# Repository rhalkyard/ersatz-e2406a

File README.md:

# Ersatz E2406A - a logic analyzer breakout for the Macintosh 68030 PDS slot

Logic analyzer adapter board for the Macintosh 68030 PDS slot, loosely based on
the [HP
E2406A](http://bitsavers.org/test_equipment/hp/logic_analyzer_preprocessors/E2406-97004_68030_Analysis_Probe_200106.pdf)
68030 analysis probe.

## Bill of materials

| Reference | Quantity | Description                                      | Digikey P/N  |
| --------- | -------- | ------------------------------------------------ | ------------ |
| J1        | 1        | DIN 41612 120 pin male connector, right-angle    | A1277-ND     |
| J2        | 1        | DIN 41612 120 pin female connector, right-angle  | A32307-ND    |
| J3-J7     | 5        | Surface-mount IDC header, 2.54mm pitch, 2x10 pin | 1175-1623-ND |

J2 is only required if additional PDS cards are to be connected.

## Compatibility

Tested and verified to work on the Macintosh SE/30.

Works (with limitations described below) on the Macintosh IIfx.

Should in theory work on the Macintosh IIsi, but has not been tested, and will
probably not fit without removing the logic board from the case.

### Logic Analyzer requirements

This adapter should be compatible with any HP logic analyzer having at least 80
channels (i.e. 5 or more pods). I have personally been using it with a 1650B and
1652B, but a 1660- or 1670-series analyzer should work just as well (or better)
so long as it has enough channels.

While it is possible to connect this board to a logic analyzer using flying-lead
pods, it is designed to be used with HP 01650-63203 "termination adapters" that
connect using 20-pin 0.1"-pitch connectors. I have also designed [a DIY
substitute](https://github.com/rhalkyard/hp-logic-analyzer-termination-adapter)
for these adapters, since they were an optional extra and most analyzers do not
come with them.

## Differences to the original E2406A

The original E2406A analysis probe is a board that interposes between the CPU
and CPU socket. Given the height of components surrounding the CPU socket on
Macintosh logic boards, it is unlikely that it would fit as intended on a
Macintosh. Instead, this adapter plugs into the 68030 PDS slot, which exposes
_almost_ the entire 68030 processor bus. The `/CIIN` and `/REFILL` signals are
not present on the PDS connector, but the absence of these signals does not have
significant bearing on analysis - on Macintosh systems, `/CIIN` is tied high,
and the `/REFILL` signal from the processor just provides additional low-level
information on the pipeline state.

The E2406A is an active probe with buffers on its logic analyzer outputs in
order to lessen its impact on signal integrity. In the interests of simplicity
(and cost), this adapter omits those buffers. On stock or minimally-expanded
machines, this appears to be no issue, but machines with large numbers of
expansion cards may experience instability.

The E2406A also has active logic to assist the analyzer in capturing accesses
that use the 68030's burst mode. This adapter omits this logic, and is unable to
correctly capture burst-mode accesses (only the final longword will be
captured). The only Macintosh to use burst mode is the IIfx, and as described
below, the architecture of the IIfx means that memory accesses cannot be
observed from the PDS slot anyway, so the lack of burst nmode support is moot in
this application.

## Limitations in use with the Macintosh IIfx

The architecture of the Macintosh IIfx imposes significant limitations on the
operation of this adapter. While on other machines, the PDS slot is connected
directly to the CPU and can fully 'observe' all bus transactions, the PDS slot
on the IIfx is on a buffered 'slow bus' separate from main memory and shared
only with NuBus and onboard I/O devices. As a result, when used on the IIfx,
this adapter can only capture accesses to PDS, NuBus and onboard I/O devices, and
cannot capture accesses to RAM or ROM.

## Configuration

Signals on the 5 20-pin pod connectors are assigned as below - note that the pod
assignments are somewhat arbitrary, but are set up to match the assignments
documented for the E2406A preprocessor.

| Pin | Pod function | J3 / Pod 1 | J4 / Pod 2 | J5 / Pod 3     | J6 / Pod 4 | J7 / Pod 5 |
| --- | ------------ | ---------- | ---------- | -------------- | ---------- | ---------- |
| 1   | +5V          | n/c        | n/c        | n/c            | n/c        | n/c        |
| 2   | n/c          | n/c        | n/c        | n/c            | n/c        | n/c        |
| 3   | Clock        | n/c        | n/c        | `/AS`          | n/c        | n/c        |
| 4   | Bit 15       | `D15`      | `D31`      | +5V (see note) | `A15`      | `A31`      |
| 5   | Bit 14       | `D14`      | `D30`      | +5V (see note) | `A14`      | `A30`      |
| 6   | Bit 13       | `D13`      | `D29`      | `/CBACK`       | `A13`      | `A29`      |
| 7   | Bit 12       | `D12`      | `D28`      | `/CBREQ`       | `A12`      | `A28`      |
| 8   | Bit 11       | `D11`      | `D27`      | `/HALT`        | `A11`      | `A27`      |
| 9   | Bit 10       | `D10`      | `D26`      | `/BERR`        | `A10`      | `A26`      |
| 10  | Bit 9        | `D9`       | `D25`      | `/STERM`       | `A9`       | `A25`      |
| 11  | Bit 8        | `D8`       | `D24`      | `/DSACK1`      | `A8`       | `A24`      |
| 12  | Bit 7        | `D7`       | `D23`      | `/DSACK0`      | `A7`       | `A23`      |
| 13  | Bit 6        | `D6`       | `D22`      | `FC2`          | `A6`       | `A22`      |
| 14  | Bit 5        | `D5`       | `D21`      | `FC1`          | `A5`       | `A21`      |
| 15  | Bit 4        | `D4`       | `D20`      | `FC0`          | `A4`       | `A20`      |
| 16  | Bit 3        | `D3`       | `D19`      | `SIZ1`         | `A3`       | `A19`      |
| 17  | Bit 2        | `D2`       | `D18`      | `SIZ0`         | `A2`       | `A18`      |
| 18  | Bit 1        | `D1`       | `D17`      | `R/W`          | `A1`       | `A17`      |
| 19  | Bit 0        | `D0`       | `D16`      | `/BGACK`       | `A0`       | `A16`      |
| 20  | GND          | GND        | GND        | GND            | GND        | GND        |

**NOTE:** The E2406A software assigns bits 15 and 14 of the processor status
lines on Pod 1 to be `/REFILL` and `/CIIN` respectively. These signals are not
exposed on the PDS connector. Since they are active-low, bits 15 and 14 are tied
to +5V so that they do not appear to be asserted. Without these signals, the
inverse assembler will not be able to identify pipeline-refill states or
external cache-inhibit assertions, but will otherwise function normally.

For state analysis, the analyzer should be clocked on a rising `/AS` signal
(i.e. a rising L clock when using the pod assignments above)

For analysis using the inverse assembler, labels must be created as follows:

| Label  | Contents                                   |
| ------ | ------------------------------------------ |
| `ADDR` | Address bits 31..0 (all bits of pods 5, 4) |
| `DATA` | Data bits 31..0 (all bits of pods 2, 1)    |
| `STAT` | Processor status (all bits of pod 3)       |

In addition to the `STAT` label, it may also be useful to create individual
labels for each status line, as shown in the pinout table.

## Inverse Assembler

The inverse assembler software for the E2406A will work with this adapter. A
disk image containing the inverse assembler can be found on BitSavers at
http://bitsavers.org/test_equipment/hp/logic_analyzer_preprocessors/inv_asm/68030.IMD.

Note that while the E2406A manual claims that it is only compatible with the
1660 series and newer, my 1652B and 1650B can run it just fine.

## (Lack of) warranty

This project is offered on an as-is, "works for me" basis. Feel free to do what
you want with it, but don't come crying to me if it makes your beloved vintage
Mac (or vintage logic analyzer) explode. If you build it for yourself, feel free
to sell any extras if you want, but I ask that you don't try to sell them for a
profit.

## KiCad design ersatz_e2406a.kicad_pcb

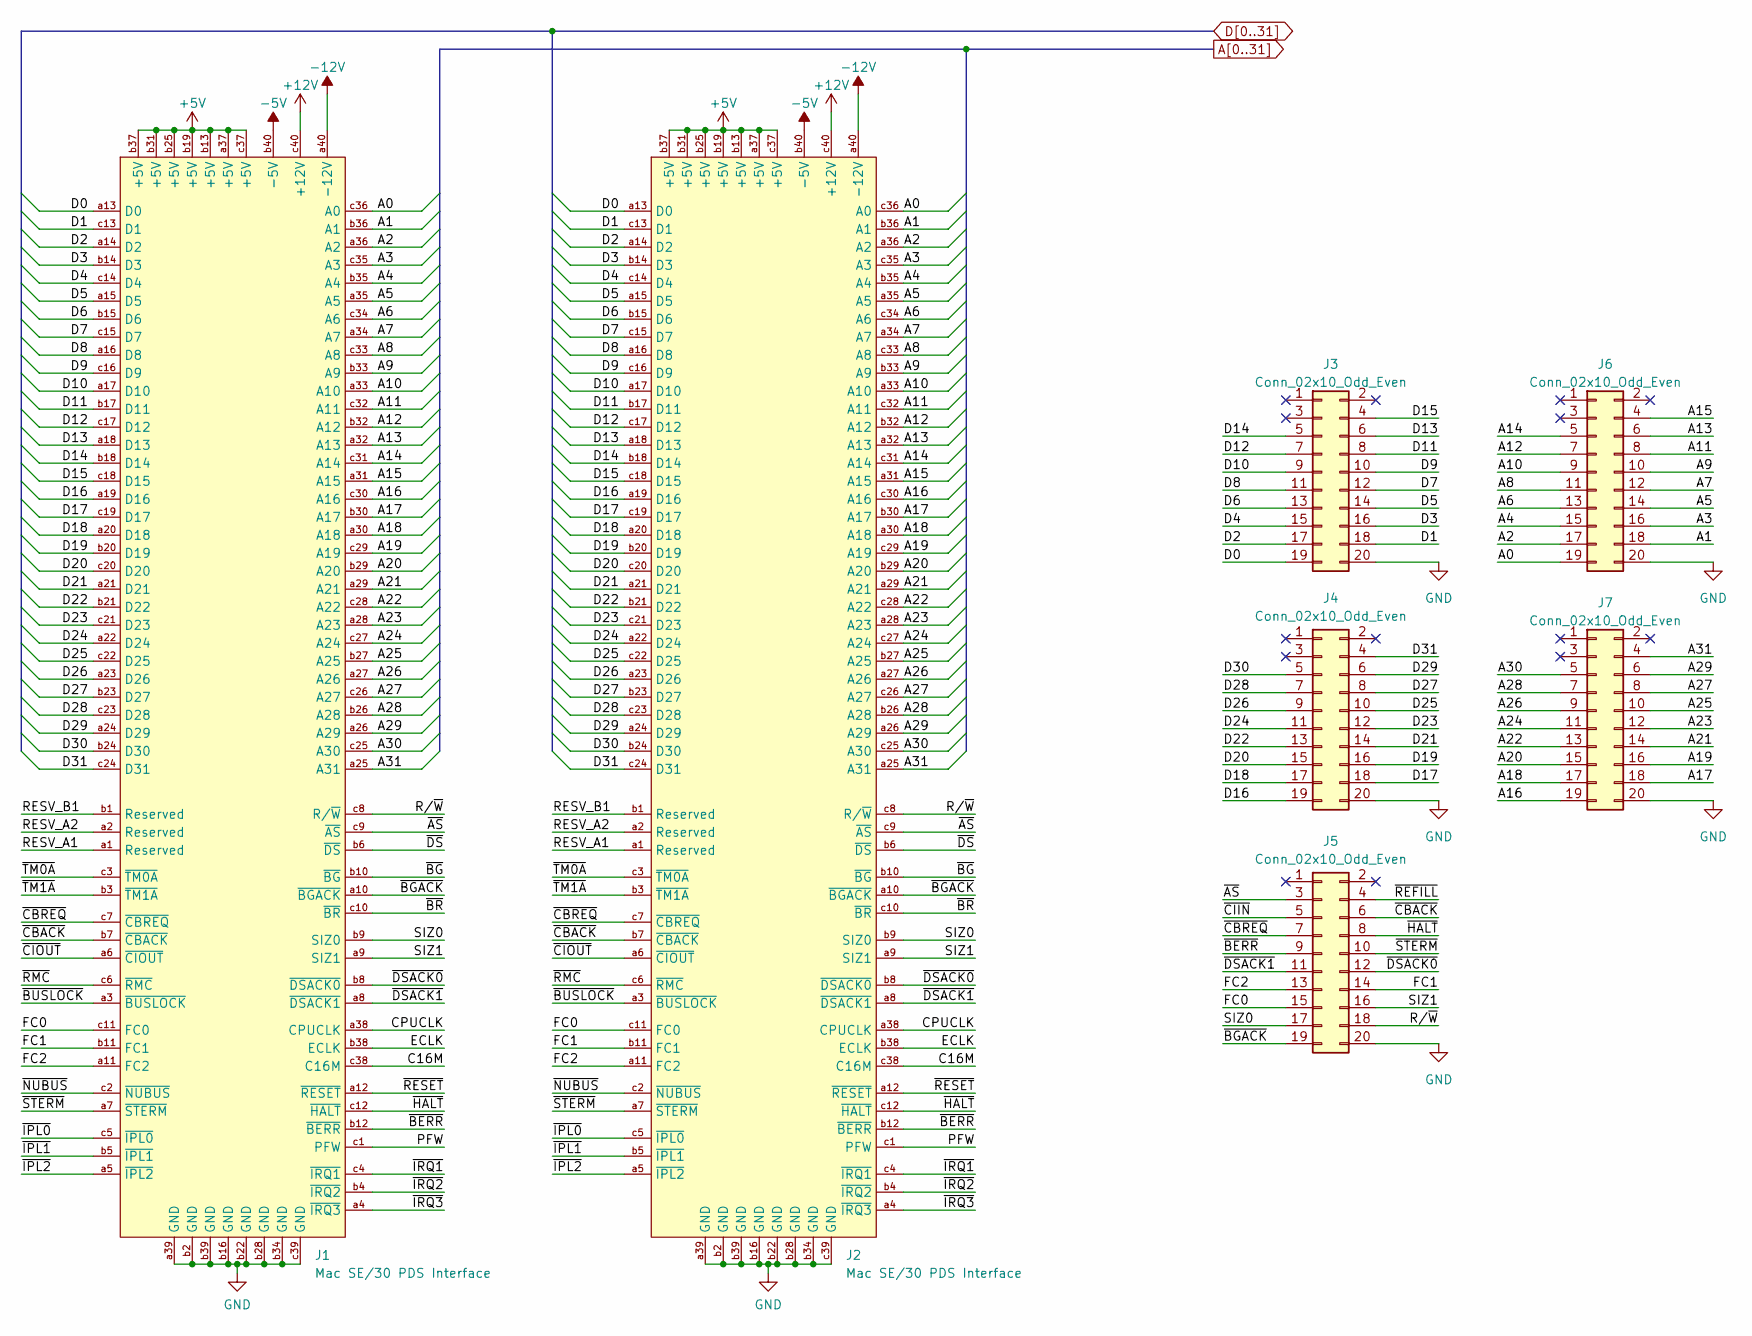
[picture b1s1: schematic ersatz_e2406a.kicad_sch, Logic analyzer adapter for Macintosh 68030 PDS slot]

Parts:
J1: Mac SE/30 PDS Interface; DIN41612_C_3x40_Male_Horizontal_THT; Digikey A1277-ND
J2: Mac SE/30 PDS Interface; DIN41612_C_3x40_Female_Horizontal_THT; Digikey A32307-ND
J3, J4, J5, J6, J7: Conn_02x10_Odd_Even; IDC-Header_2x10_P2.54mm_Vertical_SMD; Digikey 1175-1623-ND

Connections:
+5V: J1.a37 (+5V), J1.b13 (+5V), J1.b19 (+5V), J1.b25 (+5V), J1.b31 (+5V), J1.b37 (+5V), J1.c37 (+5V), J2.a37 (+5V), J2.b13 (+5V), J2.b19 (+5V), J2.b25 (+5V), J2.b31 (+5V), J2.b37 (+5V), J2.c37 (+5V)
+12V: J1.c40 (+12V), J2.c40 (+12V)
-5V: J1.b40 (-5V), J2.b40 (-5V)
-12V: J1.a40 (-12V), J2.a40 (-12V)
/C16M: J1.c38 (C16M), J2.c38 (C16M)
/CPUCLK: J1.a38 (CPUCLK), J2.a38 (CPUCLK)
/ECLK: J1.b38 (ECLK), J2.b38 (ECLK)
/FC0: J1.c11 (FC0), J2.c11 (FC0), J5.15
/FC1: J1.b11 (FC1), J2.b11 (FC1), J5.14
/FC2: J1.a11 (FC2), J2.a11 (FC2), J5.13
/PFW: J1.c1 (PFW), J2.c1 (PFW)
/RESV_A1: J1.a1 (Reserved), J2.a1 (Reserved)
/RESV_A2: J1.a2 (Reserved), J2.a2 (Reserved)
/RESV_B1: J1.b1 (Reserved), J2.b1 (Reserved)
/R/~W: J1.c8 (R/~W), J2.c8 (R/~W), J5.18
/SIZ0: J1.b9 (SIZ0), J2.b9 (SIZ0), J5.17
/SIZ1: J1.a9 (SIZ1), J2.a9 (SIZ1), J5.16
/~AS: J1.c9 (~AS), J2.c9 (~AS), J5.3
/~BERR: J1.b12 (~BERR), J2.b12 (~BERR), J5.9
/~BGACK: J1.a10 (~BGACK), J2.a10 (~BGACK), J5.19
/~BG: J1.b10 (~BG), J2.b10 (~BG)
/~BR: J1.c10 (~BR), J2.c10 (~BR)
/~BUSLOCK: J1.a3 (~BUSLOCK), J2.a3 (~BUSLOCK)
/~CBACK: J1.b7 (~CBACK), J2.b7 (~CBACK), J5.6
/~CBREQ: J1.c7 (~CBREQ), J2.c7 (~CBREQ), J5.7
/~CIIN: J5.5
/~CIOUT: J1.a6 (~CIOUT), J2.a6 (~CIOUT)
/~DSACK0: J1.b8 (~DSACK0), J2.b8 (~DSACK0), J5.12
/~DSACK1: J1.a8 (~DSACK1), J2.a8 (~DSACK1), J5.11
/~DS: J1.b6 (~DS), J2.b6 (~DS)
/~HALT: J1.c12 (~HALT), J2.c12 (~HALT), J5.8
/~IPL0: J1.c5 (~IPL0), J2.c5 (~IPL0)
/~IPL1: J1.b5 (~IPL1), J2.b5 (~IPL1)
/~IPL2: J1.a5 (~IPL2), J2.a5 (~IPL2)
/~IRQ1: J1.c4 (~IRQ1), J2.c4 (~IRQ1)
/~IRQ2: J1.b4 (~IRQ2), J2.b4 (~IRQ2)
/~IRQ3: J1.a4 (~IRQ3), J2.a4 (~IRQ3)
/~NUBUS: J1.c2 (~NUBUS), J2.c2 (~NUBUS)
/~REFILL: J5.4
/~RESET: J1.a12 (~RESET), J2.a12 (~RESET)
/~RMC: J1.c6 (~RMC), J2.c6 (~RMC)
/~STERM: J1.a7 (~STERM), J2.a7 (~STERM), J5.10
/~TM0A: J1.c3 (~TM0A), J2.c3 (~TM0A)
/~TM1A: J1.b3 (~TM1A), J2.b3 (~TM1A)
A0: J1.c36 (A0), J2.c36 (A0), J6.19
A1: J1.b36 (A1), J2.b36 (A1), J6.18
A2: J1.a36 (A2), J2.a36 (A2), J6.17
A3: J1.c35 (A3), J2.c35 (A3), J6.16
A4: J1.b35 (A4), J2.b35 (A4), J6.15
A5: J1.a35 (A5), J2.a35 (A5), J6.14
A6: J1.c34 (A6), J2.c34 (A6), J6.13
A7: J1.a34 (A7), J2.a34 (A7), J6.12
A8: J1.c33 (A8), J2.c33 (A8), J6.11
A9: J1.b33 (A9), J2.b33 (A9), J6.10
A10: J1.a33 (A10), J2.a33 (A10), J6.9
A11: J1.c32 (A11), J2.c32 (A11), J6.8
A12: J1.b32 (A12), J2.b32 (A12), J6.7
A13: J1.a32 (A13), J2.a32 (A13), J6.6
A14: J1.c31 (A14), J2.c31 (A14), J6.5
A15: J1.a31 (A15), J2.a31 (A15), J6.4
A16: J1.c30 (A16), J2.c30 (A16), J7.19
A17: J1.b30 (A17), J2.b30 (A17), J7.18
A18: J1.a30 (A18), J2.a30 (A18), J7.17
A19: J1.c29 (A19), J2.c29 (A19), J7.16
A20: J1.b29 (A20), J2.b29 (A20), J7.15
A21: J1.a29 (A21), J2.a29 (A21), J7.14
A22: J1.c28 (A22), J2.c28 (A22), J7.13
A23: J1.a28 (A23), J2.a28 (A23), J7.12
A24: J1.c27 (A24), J2.c27 (A24), J7.11
A25: J1.b27 (A25), J2.b27 (A25), J7.10
A26: J1.a27 (A26), J2.a27 (A26), J7.9
A27: J1.c26 (A27), J2.c26 (A27), J7.8
A28: J1.b26 (A28), J2.b26 (A28), J7.7
A29: J1.a26 (A29), J2.a26 (A29), J7.6
A30: J1.c25 (A30), J2.c25 (A30), J7.5
A31: J1.a25 (A31), J2.a25 (A31), J7.4
D0: J1.a13 (D0), J2.a13 (D0), J3.19
D1: J1.c13 (D1), J2.c13 (D1), J3.18
D2: J1.a14 (D2), J2.a14 (D2), J3.17
D3: J1.b14 (D3), J2.b14 (D3), J3.16
D4: J1.c14 (D4), J2.c14 (D4), J3.15
D5: J1.a15 (D5), J2.a15 (D5), J3.14
D6: J1.b15 (D6), J2.b15 (D6), J3.13
D7: J1.c15 (D7), J2.c15 (D7), J3.12
D8: J1.a16 (D8), J2.a16 (D8), J3.11
D9: J1.c16 (D9), J2.c16 (D9), J3.10
D10: J1.a17 (D10), J2.a17 (D10), J3.9
D11: J1.b17 (D11), J2.b17 (D11), J3.8
D12: J1.c17 (D12), J2.c17 (D12), J3.7
D13: J1.a18 (D13), J2.a18 (D13), J3.6
D14: J1.b18 (D14), J2.b18 (D14), J3.5
D15: J1.c18 (D15), J2.c18 (D15), J3.4
D16: J1.a19 (D16), J2.a19 (D16), J4.19
D17: J1.c19 (D17), J2.c19 (D17), J4.18
D18: J1.a20 (D18), J2.a20 (D18), J4.17
D19: J1.b20 (D19), J2.b20 (D19), J4.16
D20: J1.c20 (D20), J2.c20 (D20), J4.15
D21: J1.a21 (D21), J2.a21 (D21), J4.14
D22: J1.b21 (D22), J2.b21 (D22), J4.13
D23: J1.c21 (D23), J2.c21 (D23), J4.12
D24: J1.a22 (D24), J2.a22 (D24), J4.11
D25: J1.c22 (D25), J2.c22 (D25), J4.10
D26: J1.a23 (D26), J2.a23 (D26), J4.9
D27: J1.b23 (D27), J2.b23 (D27), J4.8
D28: J1.c23 (D28), J2.c23 (D28), J4.7
D29: J1.a24 (D29), J2.a24 (D29), J4.6
D30: J1.b24 (D30), J2.b24 (D30), J4.5
D31: J1.c24 (D31), J2.c24 (D31), J4.4
GND: J1.a39 (GND), J1.b2 (GND), J1.b16 (GND), J1.b22 (GND), J1.b28 (GND), J1.b34 (GND), J1.b39 (GND), J1.c39 (GND), J2.a39 (GND), J2.b2 (GND), J2.b16 (GND), J2.b22 (GND), J2.b28 (GND), J2.b34 (GND), J2.b39 (GND), J2.c39 (GND), J3.20, J4.20, J5.20, J6.20, J7.20

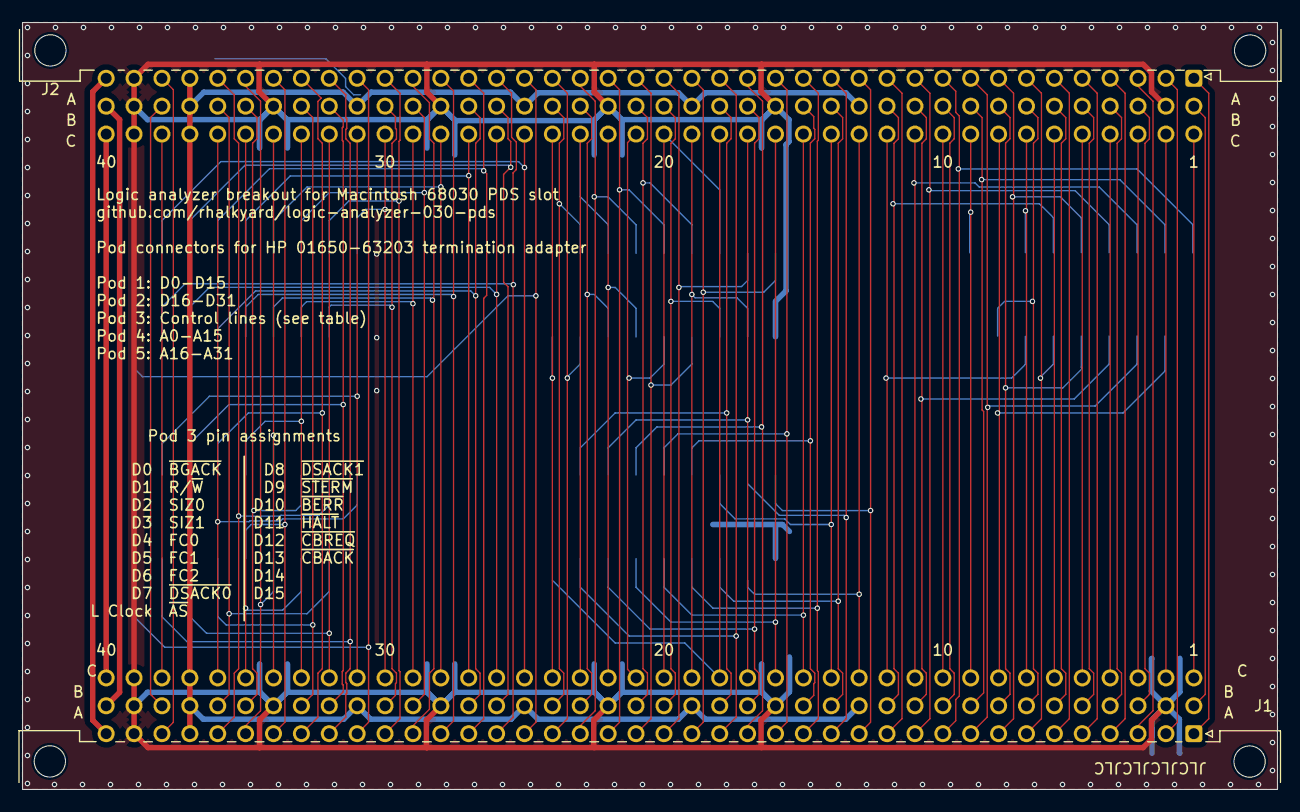
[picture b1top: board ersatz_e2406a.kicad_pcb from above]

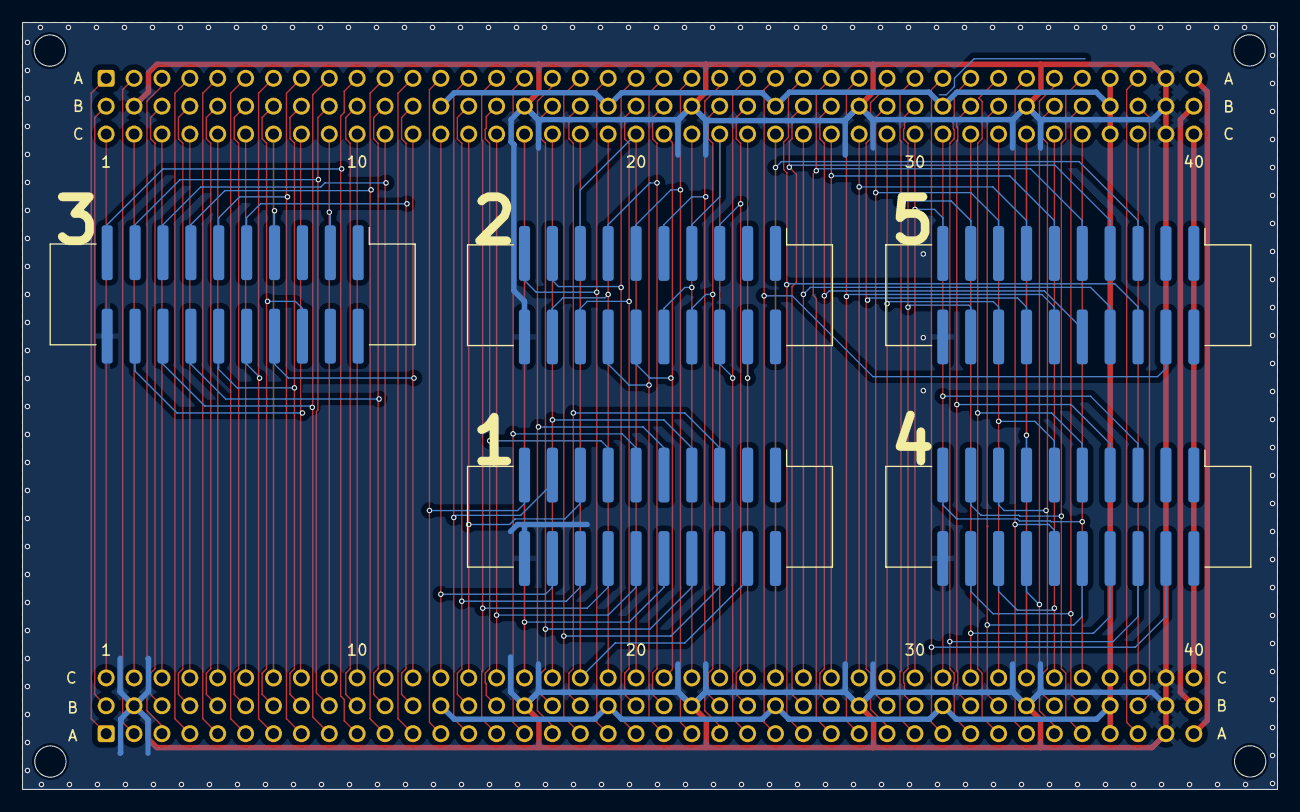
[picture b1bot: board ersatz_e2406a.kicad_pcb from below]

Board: 2 copper layers, 114.3 x 69.8 mm, 7 parts (5 on the bottom side), 107 nets.

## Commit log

2024-05-09 Docs update
